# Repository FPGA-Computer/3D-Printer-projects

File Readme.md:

This is a collection of miscellaneous projects that uses 3D printing.

All files are released under Creative Commons NonCommercial CC BY-NC license
unless otherwise stated.

https://creativecommons.org/licenses/by-nc/4.0/

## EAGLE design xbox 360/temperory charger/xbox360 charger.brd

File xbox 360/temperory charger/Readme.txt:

This is meant to be a temperory charger for the Xbox360 controller.
There are charge termination.

The battery pack is placed in the charger for an hour or so until 
the 360 controller recognizes the charge status to finish charging.

The metal contacts for the drill cradle base are from the metal strips 
that are used to crimp mesh onion bags.

https://hw-by-design.blogspot.com/2024/09/charger-adapter-for-xbox-360-battery.html

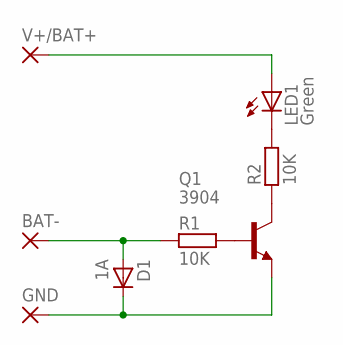
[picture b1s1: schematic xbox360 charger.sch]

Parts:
BAT-: SMD5; SMD2,54-5,08
D1: 1A; DIOM5436X265N
GND: SMD5; SMD2,54-5,08
LED1: Green; SML0603
Q1: 3904; SOT95P280X135-3N
R1, R2: 10K; RESC1608X55N
V+/BAT+: SMD5; SMD2,54-5,08

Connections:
unnamed: Q1.3 (C), R2.1
unnamed: D1.K, GND.1, Q1.2 (E)
unnamed: BAT-.1, D1.A, R1.1
unnamed: Q1.1 (B), R1.2
unnamed: LED1.C, R2.2
unnamed: LED1.A, V+/BAT+.1

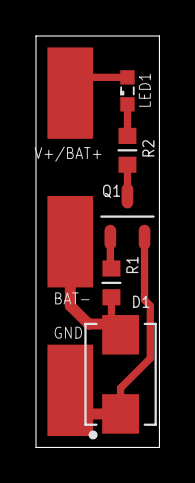
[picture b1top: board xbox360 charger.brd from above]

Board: 2 copper layers, 6.9 x 22.9 mm, 8 parts (0 on the bottom side), 6 nets.

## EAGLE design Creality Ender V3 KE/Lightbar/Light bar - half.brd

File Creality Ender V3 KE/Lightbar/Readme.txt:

I made a light strip for my 3D printer using parts I have lying around.  
It uses a LDR for sensing the ambient light level and turns on.  It also
shuts itself off for over-night print job when all other lights are off.

https://hw-by-design.blogspot.com/2024/08/3d-printer-light-strip.html

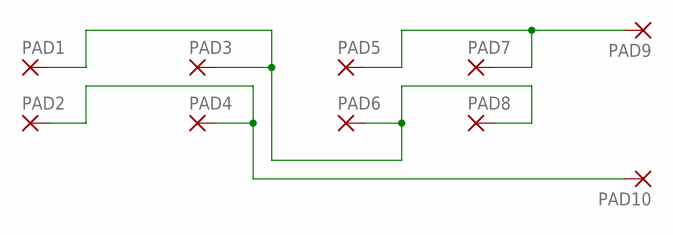
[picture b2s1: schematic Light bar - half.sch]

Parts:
PAD1, PAD2, PAD3, PAD4, PAD5, PAD6, PAD7, PAD8: SMD2; SMD1,27-2,54
PAD9, PAD10: SMD5; SMD2,54-5,08

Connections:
unnamed: PAD1.1, PAD3.1, PAD6.1, PAD8.1
unnamed: PAD2.1, PAD4.1, PAD10.1
unnamed: PAD5.1, PAD7.1, PAD9.1

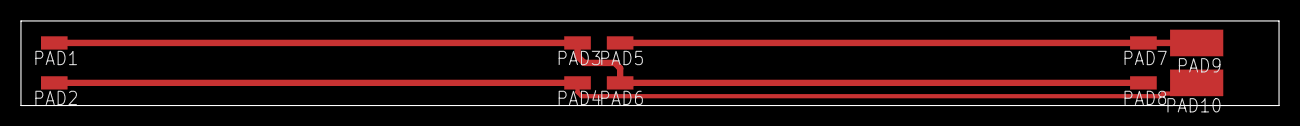
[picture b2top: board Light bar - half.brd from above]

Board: 2 copper layers, 120.0 x 8.1 mm, 10 parts (0 on the bottom side), 3 nets.

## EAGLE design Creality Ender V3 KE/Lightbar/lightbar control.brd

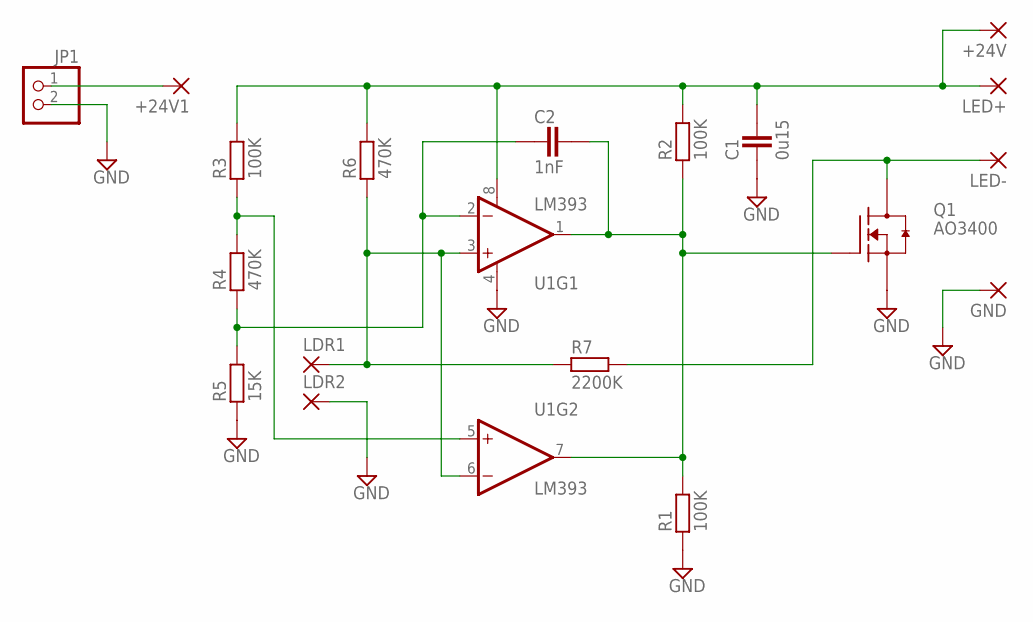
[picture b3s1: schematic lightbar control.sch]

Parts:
+24V, +24V1: SMD2; SMD1,27-2,54
C1: 0u15; CAPC2012X145AN
C2: 1nF; CAPC1608X92N
GND: SMD2; SMD1,27-2,54
JP1: PINHD-1X2/90; 1X02/90
LDR1, LDR2: SMD2; SMD1,27-2,54
LED+: SMD2; SMD1,27-2,54
LED-: SMD2; SMD1,27-2,54
Q1: AO3400; SOT95P280X135-3N
R1, R2, R3: 100K; RESC1608X55N
R4, R6: 470K; RESC1608X55N
R5: 15K; RESC1608X55N
R7: 2200K; RESC2012X70N
U1: LM393; SO08

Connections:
GND: C1.1, GND.1, JP1.2, LDR2.1, Q1.2 (S), R1.1, R5.1, U1.4 (V-)
unnamed: C2.2, Q1.1 (G), R1.2, R2.1, U1.1 (OUT), U1.7 (OUT)
unnamed: LDR1.1, R6.1, R7.1, U1.3 (+IN), U1.6 (-IN)
unnamed: R3.1, R4.2, U1.5 (+IN)
unnamed: +24V.1, C1.2, LED+.1, R2.2, R3.2, R6.2, U1.8 (V+)
unnamed: C2.1, R4.1, R5.2, U1.2 (-IN)
unnamed: LED-.1, Q1.3 (D), R7.2
unnamed: +24V1.1, JP1.1

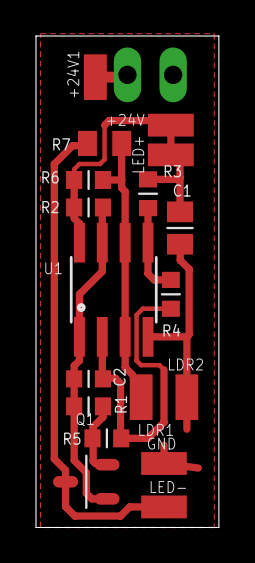
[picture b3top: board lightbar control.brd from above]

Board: 2 copper layers, 10.2 x 27.3 mm, 19 parts (1 on the bottom side), 8 nets.

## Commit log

2024-09-10 A collection of miscellaneous 3D printing projects
2025-08-11 Dockstar cooling mod
    dockstar.skb : Sketchup design file for all 3.
    ddockstar fan.stl - (repaired)Printed with regular support
    dockstar vents.stl - can be printed with or without support
    dockstar insert.stl
2025-08-11 Added Dockstar picture
2025-08-12 Models fixed
    Sketchup fan model redone. It can be exported without needing repairs.
2025-08-12 Update text to include project page
2025-08-12 Simplified fan model
    A flatten cut out to all 4 sides. This allow for different fan orientations for Sunon Maglev fan.
2025-08-14 2.5 inch removable drive caddy
    This is part of the drive bay mod project. The removable drive bay also acts as bracing for the cut panels.
2025-08-15 Sketchup file size reduction
    Clean up hidden geometry that have bloated the file size.
2025-08-17 Corsair R100 case caddy replacement
2025-08-17 added picture
2025-08-18 Wrong file extension
2025-08-18 Corrected file
2025-08-20 New caddy design
    Added 3D print tolerances, ejectors are more springy
2025-09-09 Initial release
2025-09-09 short description

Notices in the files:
parts and their libraries:
SparkFun-AnalogIC: Licensing:Creative Commons ShareAlike 4.0 International - https://creativecommons.org/licenses/by-sa/4.0
